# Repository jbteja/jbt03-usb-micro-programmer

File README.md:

# USB-Micro programmer for ESP and Arduino boards
> Image of the programmer:

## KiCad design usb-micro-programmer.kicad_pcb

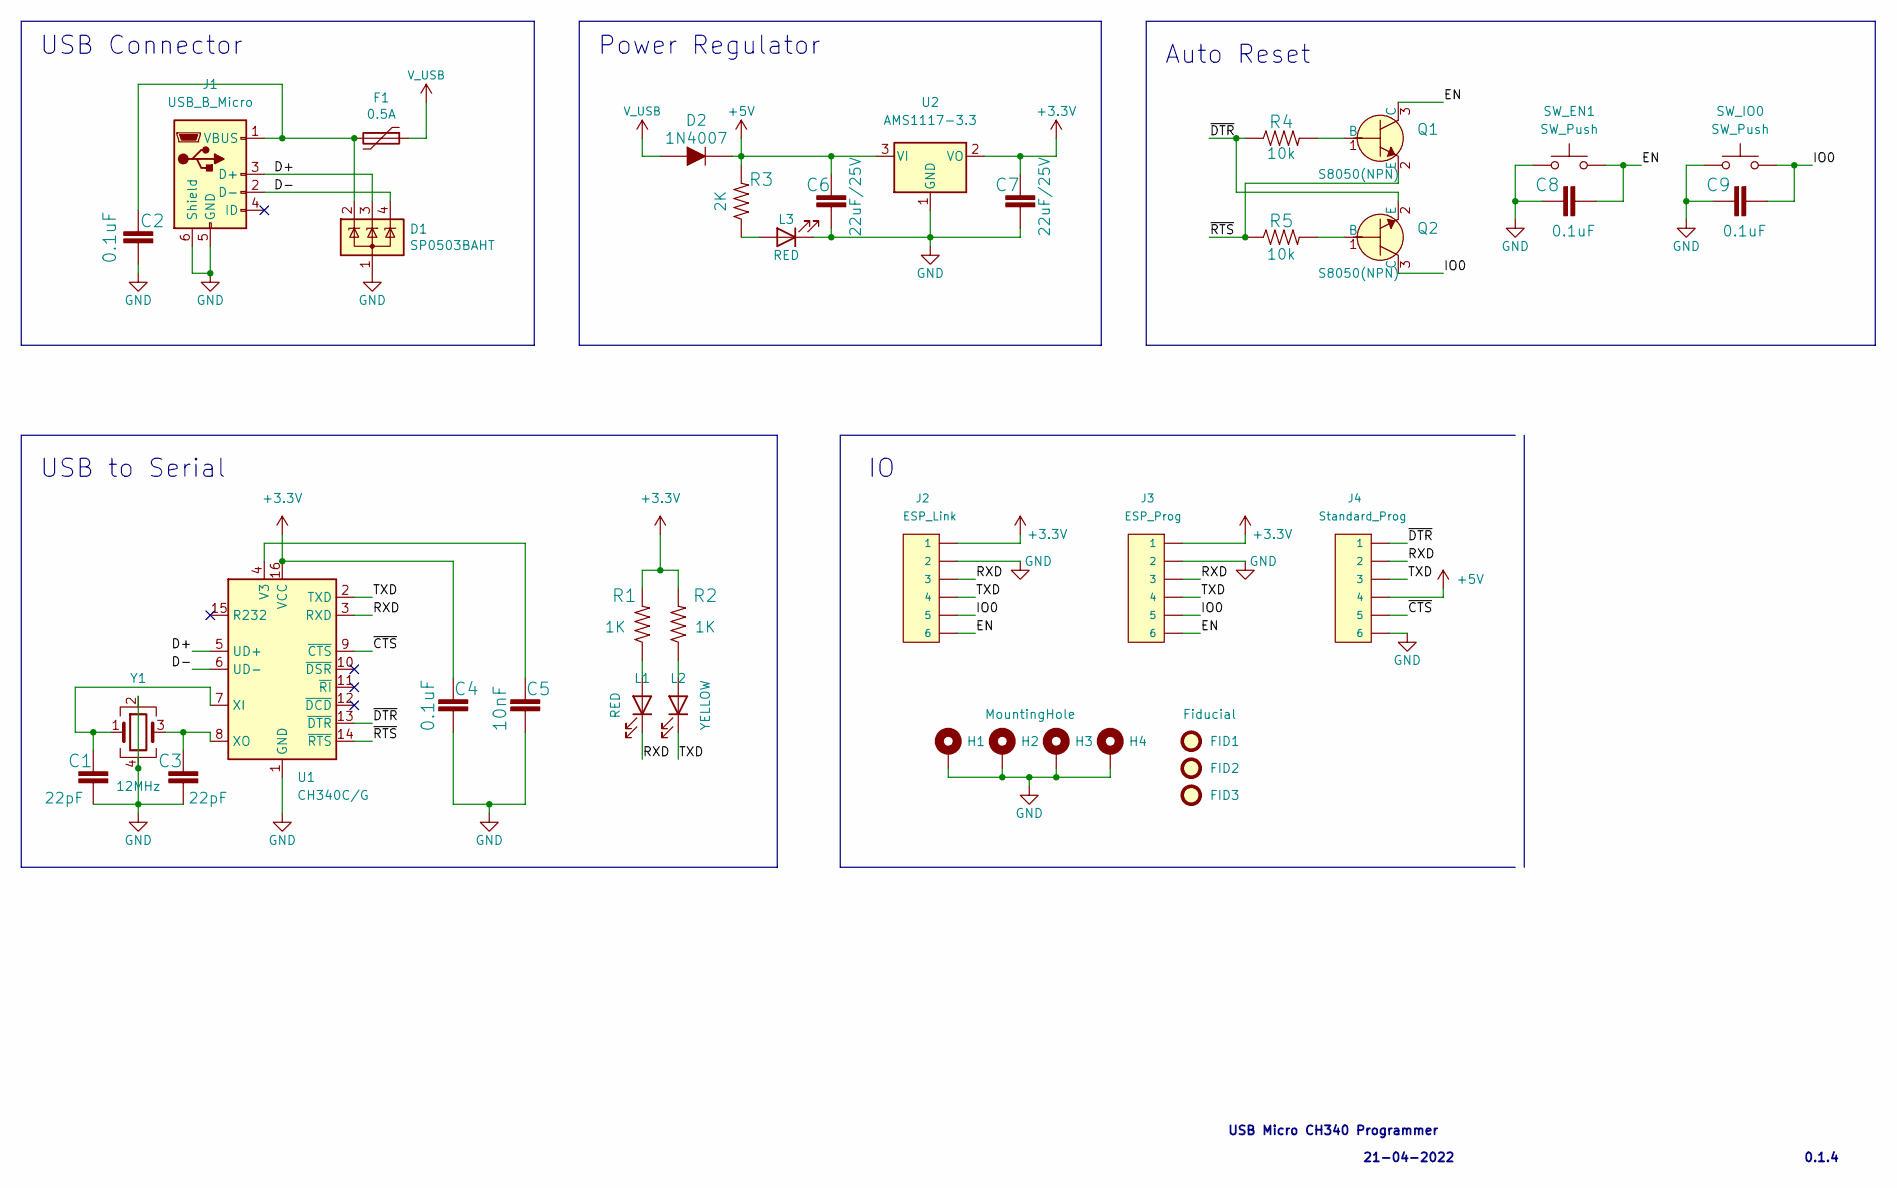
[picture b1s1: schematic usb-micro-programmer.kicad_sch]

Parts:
C1, C3: 22pF; C_0805_2012Metric_Pad1.18x1.45mm_HandSolder
C2, C4, C8, C9: 0.1uF; C_0805_2012Metric_Pad1.18x1.45mm_HandSolder
C5: 10nF; C_0805_2012Metric_Pad1.18x1.45mm_HandSolder
C6: 22uF/25V; CP_EIA-3528-21_Kemet-B_Pad1.50x2.35mm_HandSolder
C7: 22uF/25V; C_0805_2012Metric_Pad1.18x1.45mm_HandSolder
D1: SP0503BAHT; SOT-143
D2: 1N4007; DO-214AC; MPN 1N4007-T; Digi-Key_PN 1N4007DICT-ND
F1: 0.5A; Fuse_0805_2012Metric_Pad1.15x1.40mm_HandSolder
FID1, FID2, FID3: Fiducial; Fiducial_0.5mm_Mask1mm
H1, H2, H3, H4: MountingHole; MountingHole_3.2mm_M3_Pad
J1: USB_B_Micro; USB_Micro_B_Female_10118193-0001LF
J2: ESP_Link; JST_SH_SM06B-SRSS-TB_1x06-1MP_P1.00mm_Horizontal
J3: ESP_Prog; JST_EH_B6B-EH-A_1x06_P2.50mm_Vertical
J4: Standard_Prog; JST_EH_B6B-EH-A_1x06_P2.50mm_Vertical
L1, L3: RED; LED_0805_2012Metric_Pad1.15x1.40mm_HandSolder
L2: YELLOW; LED_0805_2012Metric_Pad1.15x1.40mm_HandSolder
Q1, Q2: S8050(NPN); SOT-23; MPN MMSS8050-H-TP; Digi-Key_PN MMSS8050-H-TPMSCT-ND
R1, R2: 1K; R_0805_2012Metric_Pad1.20x1.40mm_HandSolder
R3: 2K; R_0805_2012Metric_Pad1.20x1.40mm_HandSolder
R4, R5: 10k; R_0805_2012Metric_Pad1.20x1.40mm_HandSolder
SW_EN1: SW_Push; SW_PUSH_6mm_H5mm
SW_IO0: SW_Push; SW_PUSH_6mm_H5mm
U1: CH340C/G; SOIC-16_3.9x9.9mm_P1.27mm
U2: AMS1117-3.3; SOT-223-3_TabPin2
Y1: 12MHz; Crystal_SMD_3225-4Pin_3.2x2.5mm_HandSoldering

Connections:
+3V3: C4.1, C7.1, J2.1, J3.1, R1.2, R2.2, U1.16 (VCC), U2.2 (VO)
+5V: C6.1, D2.K, J4.4, R3.2, U2.3 (VI)
/D+: D1.3 (K), J1.3 (D+), U1.5 (UD+)
/D-: D1.4 (K), J1.2 (D-), U1.6 (UD-)
/EN: C8.2, J2.6, J3.6, Q1.3 (C), SW_EN1.2; also elsewhere on the board
/IO0: C9.2, J2.5, J3.5, Q2.3 (C), SW_IO0.2
/RXD: J2.3, J3.3, J4.2, L1.1 (K), U1.3 (RXD)
/TXD: J2.4, J3.4, J4.3, L2.1 (K), U1.2 (TXD)
/~CTS: J4.5, U1.9 (~CTS)
/~DTR: J4.1, Q2.2 (E), R4.1, U1.13 (~DTR)
/~RTS: Q1.2 (E), R5.1, U1.14 (~RTS)
GND: C1.2, C2.2, C3.2, C4.2, C5.2, C6.2, C7.2, C8.1, C9.1, D1.1 (A), H1.1, H2.1, H3.1, H4.1, J1.5 (GND), J1.6 (Shield), J2.2, J3.2, J4.6, L3.1 (K), SW_EN1.1, SW_IO0.1, U1.1 (GND), U2.1 (GND), Y1.2, Y1.4; also elsewhere on the board
unnamed: C1.1, U1.7 (XI), Y1.1
unnamed: C2.1, D1.2 (K), F1.2, J1.1 (VBUS)
unnamed: C3.1, U1.8 (XO), Y1.3
unnamed: C5.1, U1.4 (V3)
unnamed: L1.2 (A), R1.1
unnamed: L2.2 (A), R2.1
unnamed: L3.2 (A), R3.1
unnamed: Q1.1 (B), R4.2
unnamed: Q2.1 (B), R5.2
V_USB: D2.A, F1.1

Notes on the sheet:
USB Connector
21-04-2022
USB to Serial
0.1.4
Auto Reset
Power Regulator
USB Micro CH340 Programmer

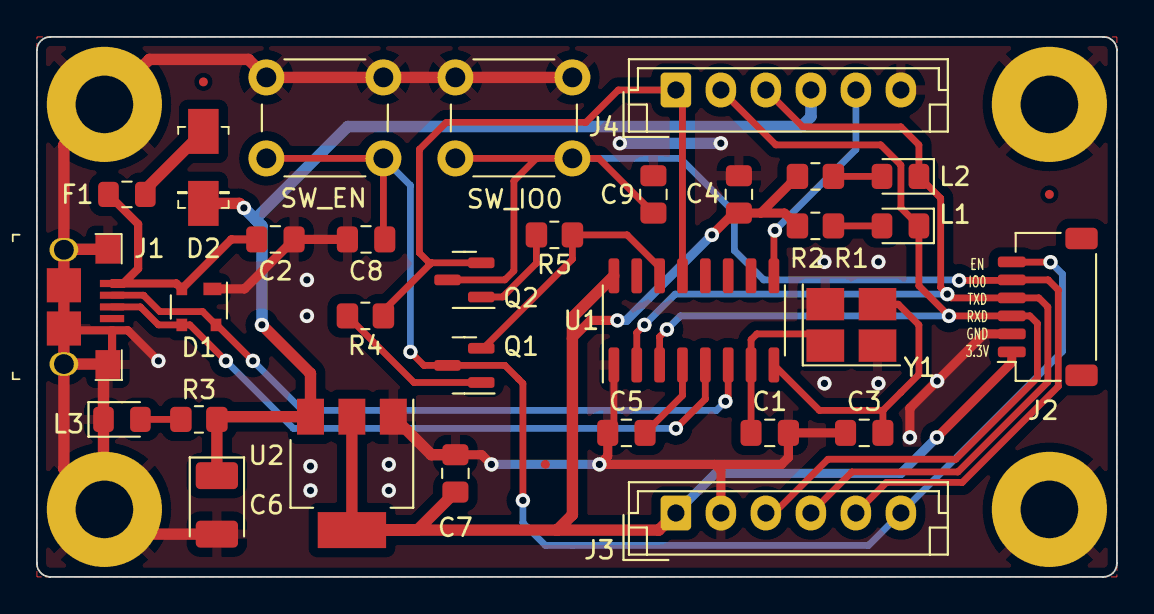
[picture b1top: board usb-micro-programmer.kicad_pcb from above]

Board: 2 copper layers, 60.0 x 30.0 mm, 38 parts (0 on the bottom side), 22 nets.

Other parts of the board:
SW_EN: SW_Push; SW_PUSH_6mm_H5mm

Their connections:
/EN: SW_EN.2; also elsewhere on the board
GND: SW_EN.1; also elsewhere on the board

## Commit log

2022-05-05 All the changes of Version 0.1.2
2022-05-05 Re-naming kicad files of version 0.1.2
2022-05-05 Deleting duplicate files
2022-05-09 Correcting changes based on gerbers
2022-05-09 Adding changes of Rev 0.1.4
2022-05-09 Adding Rev 0.1.4 Gerbers
2022-05-09 Update README.md
    Adding image to the Readme
2022-05-09 Updated Readme Rev 0.1.4
2022-05-09 Adding Rev 0.1.4 3D Image
2022-05-12 Updated rev-0.1.4 images for Readme
2022-06-11 Renaming gerber files
2023-06-13 Adding horizontal image of Rev 0.1.4
2023-06-14 Updating ignore and license file
